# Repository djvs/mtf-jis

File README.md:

# MtF-JIS Capacitive Conversion PCB for IBM Model M JIS Keyboards

Forked from ViviLazuli/mtf-capacitive

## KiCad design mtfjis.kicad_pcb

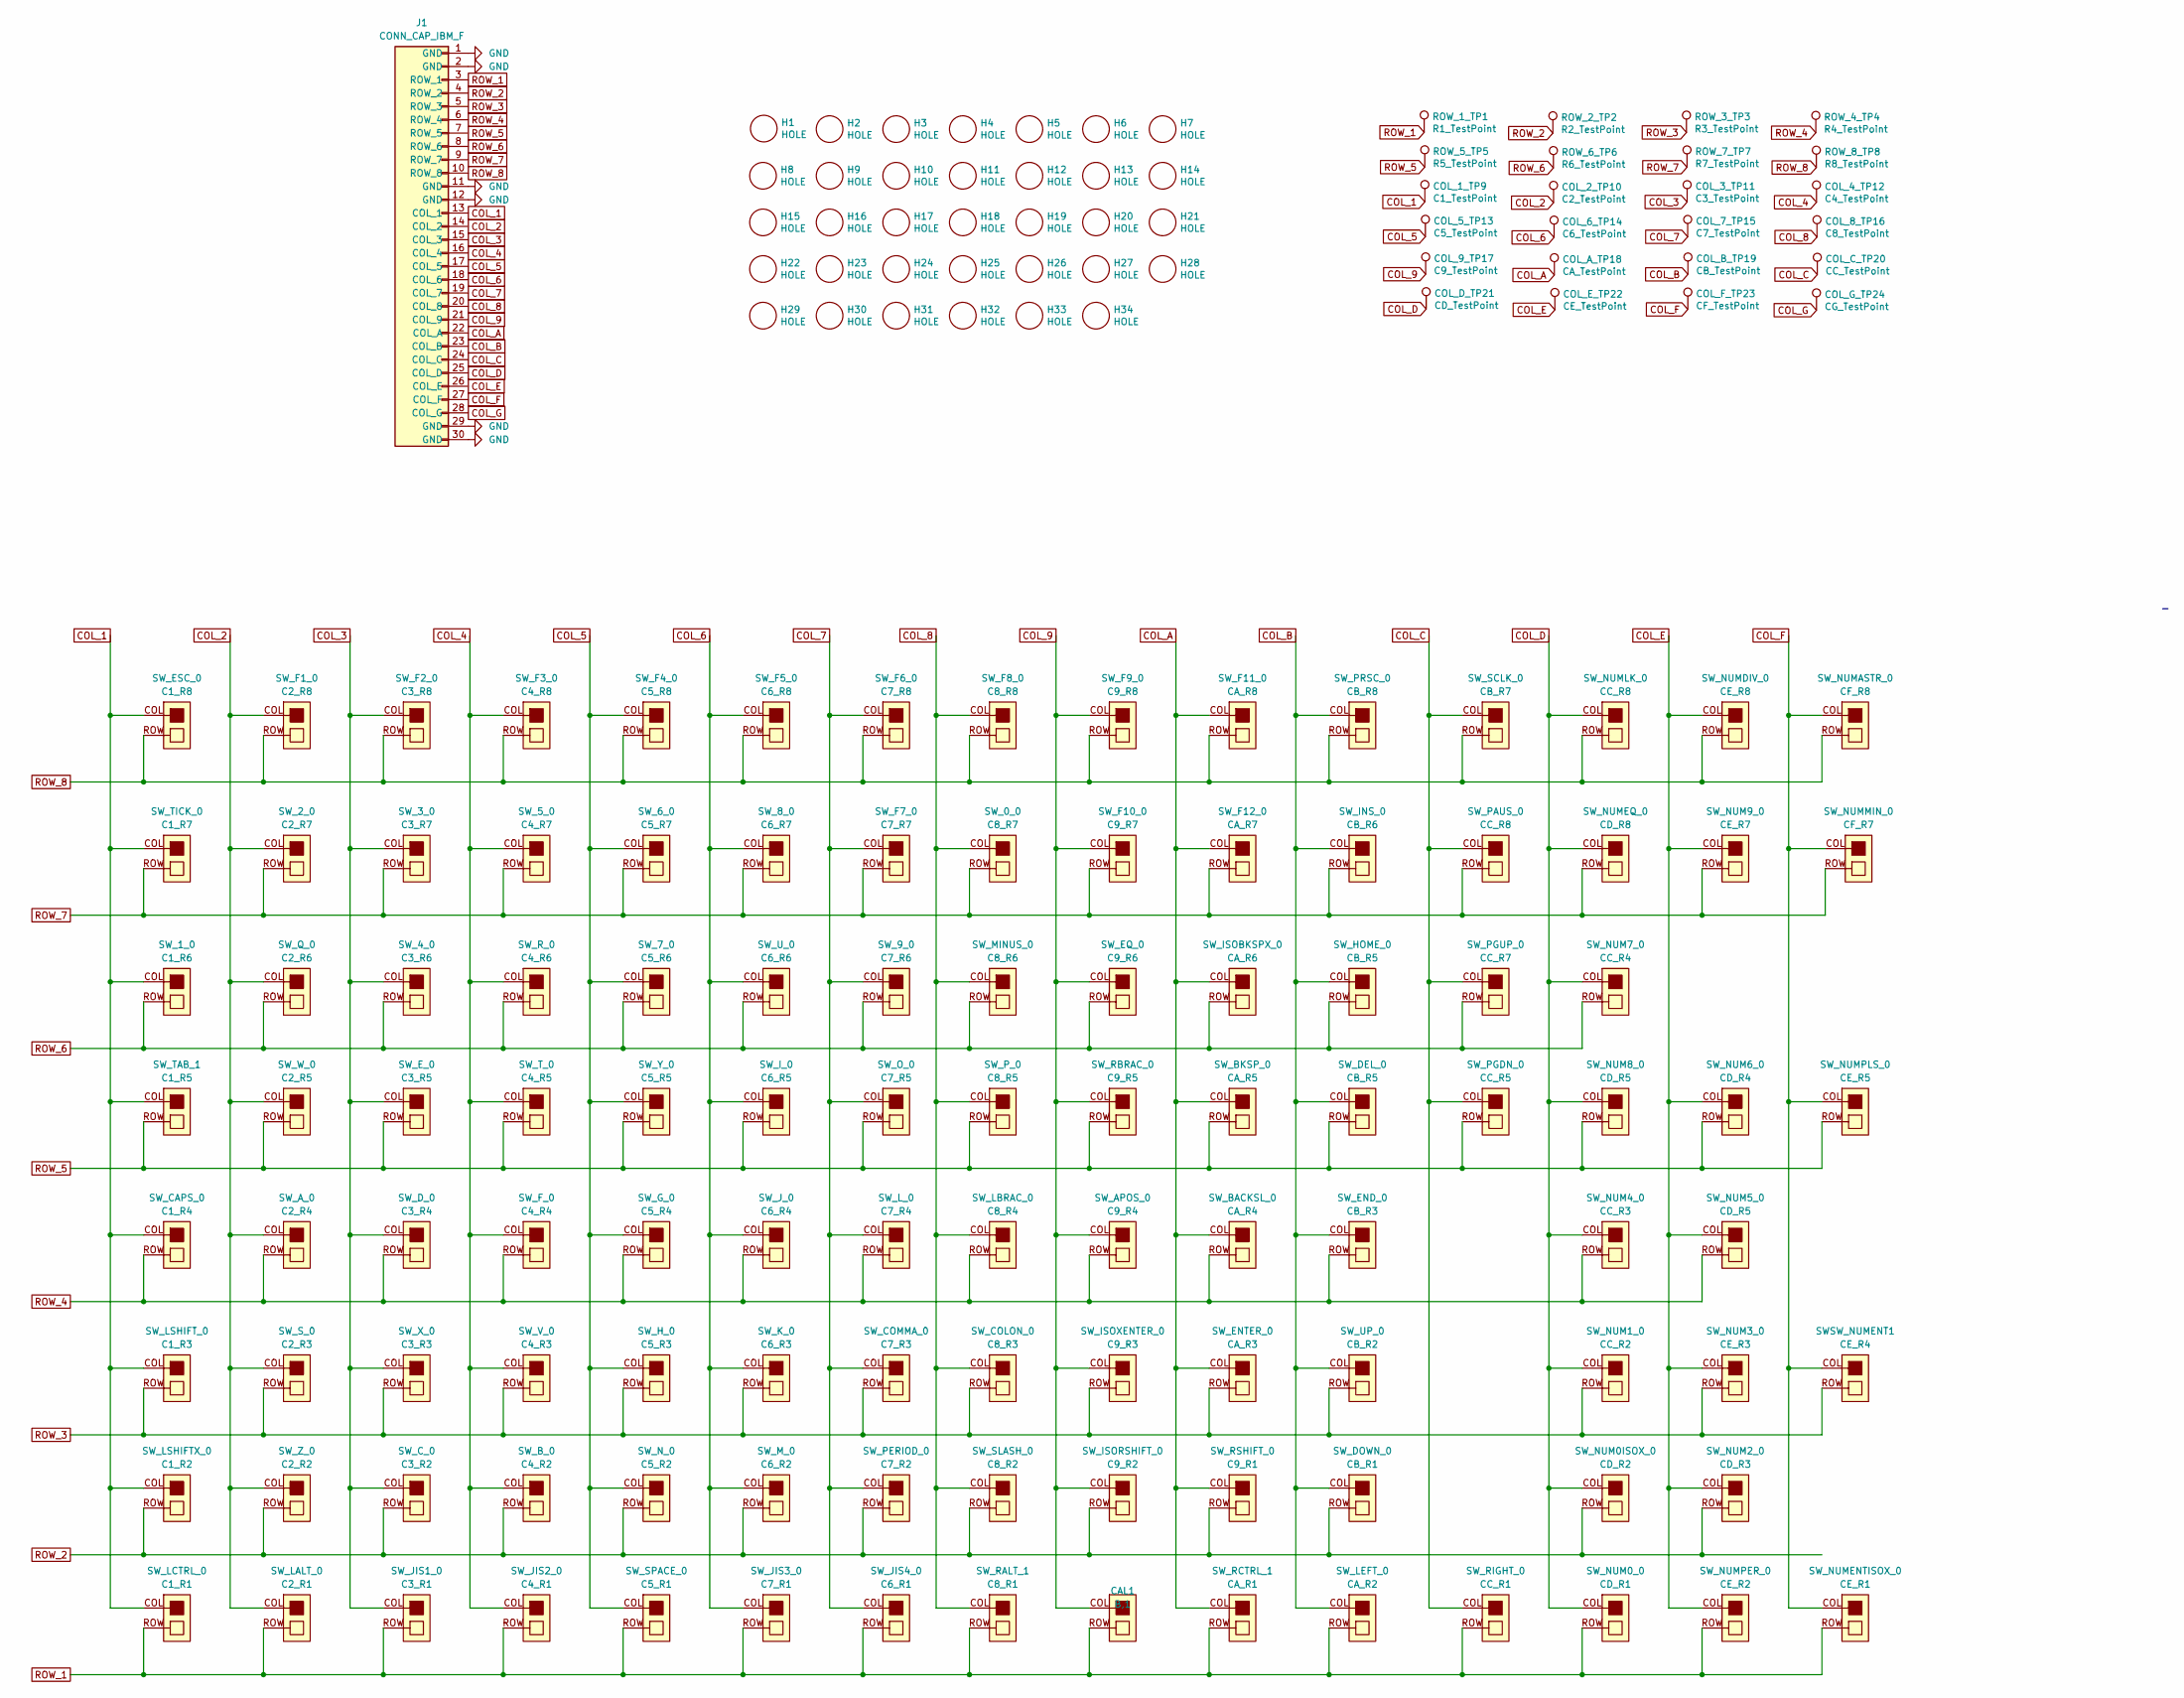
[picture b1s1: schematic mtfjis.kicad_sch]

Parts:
CAL1: B,1; CAL_CAP_IBM_F
COL_1_TP9: C1_TestPoint; TestPoint_Pad_D1.0mm
COL_2_TP10: C2_TestPoint; TestPoint_Pad_D1.0mm
COL_3_TP11: C3_TestPoint; TestPoint_Pad_D1.0mm
COL_4_TP12: C4_TestPoint; TestPoint_Pad_D1.0mm
COL_5_TP13: C5_TestPoint; TestPoint_Pad_D1.0mm
COL_6_TP14: C6_TestPoint; TestPoint_Pad_D1.0mm
COL_7_TP15: C7_TestPoint; TestPoint_Pad_D1.0mm
COL_8_TP16: C8_TestPoint; TestPoint_Pad_D1.0mm
COL_9_TP17: C9_TestPoint; TestPoint_Pad_D1.0mm
COL_A_TP18: CA_TestPoint; TestPoint_Pad_D1.0mm
COL_B_TP19: CB_TestPoint; TestPoint_Pad_D1.0mm
COL_C_TP20: CC_TestPoint; TestPoint_Pad_D1.0mm
COL_D_TP21: CD_TestPoint; TestPoint_Pad_D1.0mm
COL_E_TP22: CE_TestPoint; TestPoint_Pad_D1.0mm
COL_F_TP23: CF_TestPoint; TestPoint_Pad_D1.0mm
COL_G_TP24: CG_TestPoint; TestPoint_Pad_D1.0mm
H1, H2, H3, H4, H5, H6, H7, H8, H9, H10, H11, H12, H13, H14, H15, H16, H17, H18, H19, H20, H21, H22, H23, H24, H25, H26, H27, H28, H29, H30, H31, H32, H33, H34: HOLE
J1: CONN_CAP_IBM_F
ROW_1_TP1: R1_TestPoint; TestPoint_Pad_D1.0mm
ROW_2_TP2: R2_TestPoint; TestPoint_Pad_D1.0mm
ROW_3_TP3: R3_TestPoint; TestPoint_Pad_D1.0mm
ROW_4_TP4: R4_TestPoint; TestPoint_Pad_D1.0mm
ROW_5_TP5: R5_TestPoint; TestPoint_Pad_D1.0mm
ROW_6_TP6: R6_TestPoint; TestPoint_Pad_D1.0mm
ROW_7_TP7: R7_TestPoint; TestPoint_Pad_D1.0mm
ROW_8_TP8: R8_TestPoint; TestPoint_Pad_D1.0mm
SWSW_NUMENT1: CE_R4; SW_CAP_IBM_F
SW_0_0: C8_R7; SW_CAP_IBM_F
SW_1_0: C1_R6; SW_CAP_IBM_F_ALT
SW_2_0: C2_R7; SW_CAP_IBM_F
SW_3_0: C3_R7; SW_CAP_IBM_F
SW_4_0: C3_R6; SW_CAP_IBM_F_ALT
SW_5_0: C4_R7; SW_CAP_IBM_F
SW_6_0: C5_R7; SW_CAP_IBM_F
SW_7_0: C5_R6; SW_CAP_IBM_F_ALT
SW_8_0: C6_R7; SW_CAP_IBM_F_ALT
SW_9_0: C7_R6; SW_CAP_IBM_F_ALT
SW_APOS_0: C9_R4; SW_CAP_IBM_F
SW_A_0: C2_R4; SW_CAP_IBM_F
SW_BACKSL_0: CA_R4; SW_CAP_IBM_F
SW_BKSP_0: CA_R5; SW_CAP_IBM_F_ALT
SW_B_0: C4_R2; SW_CAP_IBM_F_ALT
SW_CAPS_0: C1_R4; SW_CAP_IBM_F
SW_COLON_0: C8_R3; SW_CAP_IBM_F
SW_COMMA_0: C7_R3; SW_CAP_IBM_F
SW_C_0: C3_R2; SW_CAP_IBM_F_ALT
SW_DEL_0: CB_R5; SW_CAP_IBM_F
SW_DOWN_0: CB_R1; SW_CAP_IBM_F_ALT
SW_D_0: C3_R4; SW_CAP_IBM_F
SW_END_0: CB_R3; SW_CAP_IBM_F_ALT
SW_ENTER_0: CA_R3; SW_CAP_IBM_F
SW_EQ_0: C9_R6; SW_CAP_IBM_F_ALT
SW_ESC_0: C1_R8; SW_CAP_IBM_F
SW_E_0: C3_R5; SW_CAP_IBM_F
SW_F1_0: C2_R8; SW_CAP_IBM_F
SW_F2_0: C3_R8; SW_CAP_IBM_F
SW_F3_0: C4_R8; SW_CAP_IBM_F_ALT
SW_F4_0: C5_R8; SW_CAP_IBM_F
SW_F5_0: C6_R8; SW_CAP_IBM_F
SW_F6_0: C7_R8; SW_CAP_IBM_F
SW_F7_0: C7_R7; SW_CAP_IBM_F_ALT
SW_F8_0: C8_R8; SW_CAP_IBM_F
SW_F9_0: C9_R8; SW_CAP_IBM_F
SW_F10_0: C9_R7; SW_CAP_IBM_F_ALT
SW_F11_0: CA_R8; SW_CAP_IBM_F
SW_F12_0: CA_R7; SW_CAP_IBM_F_ALT
SW_F_0: C4_R4; SW_CAP_IBM_F
SW_G_0: C5_R4; SW_CAP_IBM_F
SW_HOME_0: CB_R5; SW_CAP_IBM_F_ALT
SW_H_0: C5_R3; SW_CAP_IBM_F_ALT
SW_INS_0: CB_R6; SW_CAP_IBM_F
SW_ISOBKSPX_0: CA_R6; SW_CAP_IBM_F
SW_ISORSHIFT_0: C9_R2; SW_CAP_IBM_F
SW_ISOXENTER_0: C9_R3; SW_CAP_IBM_F_ALT
SW_I_0: C6_R5; SW_CAP_IBM_F_ALT
SW_JIS1_0: C3_R1; SW_CAP_IBM_F_ALT
SW_JIS2_0: C4_R1; SW_CAP_IBM_F_ALT
SW_JIS3_0: C7_R1; SW_CAP_IBM_F_ALT
SW_JIS4_0: C6_R1; SW_CAP_IBM_F_ALT
SW_J_0: C6_R4; SW_CAP_IBM_F
SW_K_0: C6_R3; SW_CAP_IBM_F_ALT
SW_LALT_0: C2_R1; SW_CAP_IBM_F_ALT
SW_LBRAC_0: C8_R4; SW_CAP_IBM_F_ALT
SW_LCTRL_0: C1_R1; SW_CAP_IBM_F
SW_LEFT_0: CA_R2; SW_CAP_IBM_F
SW_LSHIFTX_0: C1_R2; SW_CAP_IBM_F_ALT
SW_LSHIFT_0: C1_R3; SW_CAP_IBM_F
SW_L_0: C7_R4; SW_CAP_IBM_F_ALT
SW_MINUS_0: C8_R6; SW_CAP_IBM_F_ALT
SW_M_0: C6_R2; SW_CAP_IBM_F_ALT
SW_NUM0ISOX_0: CD_R2; SW_CAP_IBM_F_ALT
SW_NUM0_0: CD_R1; SW_CAP_IBM_F
SW_NUM1_0: CC_R2; SW_CAP_IBM_F
SW_NUM2_0: CD_R3; SW_CAP_IBM_F
SW_NUM3_0: CE_R3; SW_CAP_IBM_F_ALT
SW_NUM4_0: CC_R3; SW_CAP_IBM_F
SW_NUM5_0: CD_R5; SW_CAP_IBM_F
SW_NUM6_0: CD_R4; SW_CAP_IBM_F_ALT
SW_NUM7_0: CC_R4; SW_CAP_IBM_F
SW_NUM8_0: CD_R5; SW_CAP_IBM_F_ALT
SW_NUM9_0: CE_R7; SW_CAP_IBM_F
SW_NUMASTR_0: CF_R8; SW_CAP_IBM_F
SW_NUMDIV_0: CE_R8; SW_CAP_IBM_F
SW_NUMENTISOX_0: CE_R1; SW_CAP_IBM_F
SW_NUMEQ_0: CD_R8; SW_CAP_IBM_F_ALT
SW_NUMLK_0: CC_R8; SW_CAP_IBM_F
SW_NUMMIN_0: CF_R7; SW_CAP_IBM_F
SW_NUMPER_0: CE_R2; SW_CAP_IBM_F_ALT
SW_NUMPLS_0: CE_R5; SW_CAP_IBM_F
SW_N_0: C5_R2; SW_CAP_IBM_F_ALT
SW_O_0: C7_R5; SW_CAP_IBM_F_ALT
SW_PAUS_0: CC_R8; SW_CAP_IBM_F_ALT
SW_PERIOD_0: C7_R2; SW_CAP_IBM_F_ALT
SW_PGDN_0: CC_R5; SW_CAP_IBM_F
SW_PGUP_0: CC_R7; SW_CAP_IBM_F
SW_PRSC_0: CB_R8; SW_CAP_IBM_F
SW_P_0: C8_R5; SW_CAP_IBM_F
SW_Q_0: C2_R6; SW_CAP_IBM_F_ALT
SW_RALT_1: C8_R1; SW_CAP_IBM_F_ALT
SW_RBRAC_0: C9_R5; SW_CAP_IBM_F_ALT
SW_RCTRL_1: CA_R1; SW_CAP_IBM_F
SW_RIGHT_0: CC_R1; SW_CAP_IBM_F
SW_RSHIFT_0: C9_R1; SW_CAP_IBM_F
SW_R_0: C4_R6; SW_CAP_IBM_F
SW_SCLK_0: CB_R7; SW_CAP_IBM_F
SW_SLASH_0: C8_R2; SW_CAP_IBM_F_ALT
SW_SPACE_0: C5_R1; SW_CAP_IBM_F_ALT
SW_S_0: C2_R3; SW_CAP_IBM_F_ALT
SW_TAB_1: C1_R5; SW_CAP_IBM_F
SW_TICK_0: C1_R7; SW_CAP_IBM_F
SW_T_0: C4_R5; SW_CAP_IBM_F_ALT
SW_UP_0: CB_R2; SW_CAP_IBM_F_ALT
SW_U_0: C6_R6; SW_CAP_IBM_F
SW_V_0: C4_R3; SW_CAP_IBM_F
SW_W_0: C2_R5; SW_CAP_IBM_F
SW_X_0: C3_R3; SW_CAP_IBM_F
SW_Y_0: C5_R5; SW_CAP_IBM_F_ALT
SW_Z_0: C2_R2; SW_CAP_IBM_F

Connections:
COL_1: COL_1_TP9.1, J1.13 (COL_1), SW_1_0.COL, SW_CAPS_0.COL, SW_ESC_0.COL, SW_LCTRL_0.COL, SW_LSHIFTX_0.COL, SW_LSHIFT_0.COL, SW_TAB_1.COL, SW_TICK_0.COL
COL_2: COL_2_TP10.1, J1.14 (COL_2), SW_2_0.COL, SW_A_0.COL, SW_F1_0.COL, SW_LALT_0.COL, SW_Q_0.COL, SW_S_0.COL, SW_W_0.COL, SW_Z_0.COL
COL_3: COL_3_TP11.1, J1.15 (COL_3), SW_3_0.COL, SW_4_0.COL, SW_C_0.COL, SW_D_0.COL, SW_E_0.COL, SW_F2_0.COL, SW_JIS1_0.COL, SW_X_0.COL
COL_4: COL_4_TP12.1, J1.16 (COL_4), SW_5_0.COL, SW_B_0.COL, SW_F3_0.COL, SW_F_0.COL, SW_JIS2_0.COL, SW_R_0.COL, SW_T_0.COL, SW_V_0.COL
COL_5: COL_5_TP13.1, J1.17 (COL_5), SW_6_0.COL, SW_7_0.COL, SW_F4_0.COL, SW_G_0.COL, SW_H_0.COL, SW_N_0.COL, SW_SPACE_0.COL, SW_Y_0.COL
COL_6: COL_6_TP14.1, J1.18 (COL_6), SW_8_0.COL, SW_F5_0.COL, SW_I_0.COL, SW_JIS3_0.COL, SW_J_0.COL, SW_K_0.COL, SW_M_0.COL, SW_U_0.COL
COL_7: COL_7_TP15.1, J1.19 (COL_7), SW_9_0.COL, SW_COMMA_0.COL, SW_F6_0.COL, SW_F7_0.COL, SW_JIS4_0.COL, SW_L_0.COL, SW_O_0.COL, SW_PERIOD_0.COL
COL_8: COL_8_TP16.1, J1.20 (COL_8), SW_0_0.COL, SW_COLON_0.COL, SW_F8_0.COL, SW_LBRAC_0.COL, SW_MINUS_0.COL, SW_P_0.COL, SW_RALT_1.COL, SW_SLASH_0.COL
COL_9: CAL1.COL, COL_9_TP17.1, J1.21 (COL_9), SW_APOS_0.COL, SW_EQ_0.COL, SW_F9_0.COL, SW_F10_0.COL, SW_ISORSHIFT_0.COL, SW_ISOXENTER_0.COL, SW_RBRAC_0.COL
COL_A: COL_A_TP18.1, J1.22 (COL_A), SW_BACKSL_0.COL, SW_BKSP_0.COL, SW_ENTER_0.COL, SW_F11_0.COL, SW_F12_0.COL, SW_ISOBKSPX_0.COL, SW_RCTRL_1.COL, SW_RSHIFT_0.COL
COL_B: COL_B_TP19.1, J1.23 (COL_B), SW_DEL_0.COL, SW_DOWN_0.COL, SW_END_0.COL, SW_HOME_0.COL, SW_INS_0.COL, SW_LEFT_0.COL, SW_PRSC_0.COL, SW_UP_0.COL
COL_C: COL_C_TP20.1, J1.24 (COL_C), SW_PAUS_0.COL, SW_PGDN_0.COL, SW_PGUP_0.COL, SW_RIGHT_0.COL, SW_SCLK_0.COL
COL_D: COL_D_TP21.1, J1.25 (COL_D), SW_NUM0ISOX_0.COL, SW_NUM0_0.COL, SW_NUM1_0.COL, SW_NUM4_0.COL, SW_NUM7_0.COL, SW_NUM8_0.COL, SW_NUMEQ_0.COL, SW_NUMLK_0.COL
COL_E: COL_E_TP22.1, J1.26 (COL_E), SW_NUM2_0.COL, SW_NUM3_0.COL, SW_NUM5_0.COL, SW_NUM6_0.COL, SW_NUM9_0.COL, SW_NUMDIV_0.COL, SW_NUMPER_0.COL
COL_F: COL_F_TP23.1, J1.27 (COL_F), SWSW_NUMENT1.COL, SW_NUMASTR_0.COL, SW_NUMENTISOX_0.COL, SW_NUMMIN_0.COL, SW_NUMPLS_0.COL
COL_G: COL_G_TP24.1, J1.28 (COL_G)
GND: J1.1 (GND), J1.2 (GND), J1.11 (GND), J1.12 (GND), J1.29 (GND), J1.30 (GND)
ROW_1: CAL1.ROW, J1.3 (ROW_1), ROW_1_TP1.1, SW_JIS1_0.ROW, SW_JIS2_0.ROW, SW_JIS3_0.ROW, SW_JIS4_0.ROW, SW_LALT_0.ROW, SW_LCTRL_0.ROW, SW_LEFT_0.ROW, SW_NUM0_0.ROW, SW_NUMENTISOX_0.ROW, SW_NUMPER_0.ROW, SW_RALT_1.ROW, SW_RCTRL_1.ROW, SW_RIGHT_0.ROW, SW_SPACE_0.ROW
ROW_2: J1.4 (ROW_2), ROW_2_TP2.1, SW_B_0.ROW, SW_C_0.ROW, SW_DOWN_0.ROW, SW_ISORSHIFT_0.ROW, SW_LSHIFTX_0.ROW, SW_M_0.ROW, SW_NUM0ISOX_0.ROW, SW_NUM2_0.ROW, SW_N_0.ROW, SW_PERIOD_0.ROW, SW_RSHIFT_0.ROW, SW_SLASH_0.ROW, SW_Z_0.ROW
ROW_3: J1.5 (ROW_3), ROW_3_TP3.1, SWSW_NUMENT1.ROW, SW_COLON_0.ROW, SW_COMMA_0.ROW, SW_ENTER_0.ROW, SW_H_0.ROW, SW_ISOXENTER_0.ROW, SW_K_0.ROW, SW_LSHIFT_0.ROW, SW_NUM1_0.ROW, SW_NUM3_0.ROW, SW_S_0.ROW, SW_UP_0.ROW, SW_V_0.ROW, SW_X_0.ROW
ROW_4: J1.6 (ROW_4), ROW_4_TP4.1, SW_APOS_0.ROW, SW_A_0.ROW, SW_BACKSL_0.ROW, SW_CAPS_0.ROW, SW_D_0.ROW, SW_END_0.ROW, SW_F_0.ROW, SW_G_0.ROW, SW_J_0.ROW, SW_LBRAC_0.ROW, SW_L_0.ROW, SW_NUM4_0.ROW, SW_NUM5_0.ROW
ROW_5: J1.7 (ROW_5), ROW_5_TP5.1, SW_BKSP_0.ROW, SW_DEL_0.ROW, SW_E_0.ROW, SW_I_0.ROW, SW_NUM6_0.ROW, SW_NUM8_0.ROW, SW_NUMPLS_0.ROW, SW_O_0.ROW, SW_PGDN_0.ROW, SW_P_0.ROW, SW_RBRAC_0.ROW, SW_TAB_1.ROW, SW_T_0.ROW, SW_W_0.ROW, SW_Y_0.ROW
ROW_6: J1.8 (ROW_6), ROW_6_TP6.1, SW_1_0.ROW, SW_4_0.ROW, SW_7_0.ROW, SW_9_0.ROW, SW_EQ_0.ROW, SW_HOME_0.ROW, SW_ISOBKSPX_0.ROW, SW_MINUS_0.ROW, SW_NUM7_0.ROW, SW_PGUP_0.ROW, SW_Q_0.ROW, SW_R_0.ROW, SW_U_0.ROW
ROW_7: J1.9 (ROW_7), ROW_7_TP7.1, SW_0_0.ROW, SW_2_0.ROW, SW_3_0.ROW, SW_5_0.ROW, SW_6_0.ROW, SW_8_0.ROW, SW_F7_0.ROW, SW_F10_0.ROW, SW_F12_0.ROW, SW_INS_0.ROW, SW_NUM9_0.ROW, SW_NUMEQ_0.ROW, SW_NUMMIN_0.ROW, SW_PAUS_0.ROW, SW_TICK_0.ROW
ROW_8: J1.10 (ROW_8), ROW_8_TP8.1, SW_ESC_0.ROW, SW_F1_0.ROW, SW_F2_0.ROW, SW_F3_0.ROW, SW_F4_0.ROW, SW_F5_0.ROW, SW_F6_0.ROW, SW_F8_0.ROW, SW_F9_0.ROW, SW_F11_0.ROW, SW_NUMASTR_0.ROW, SW_NUMDIV_0.ROW, SW_NUMLK_0.ROW, SW_PRSC_0.ROW, SW_SCLK_0.ROW

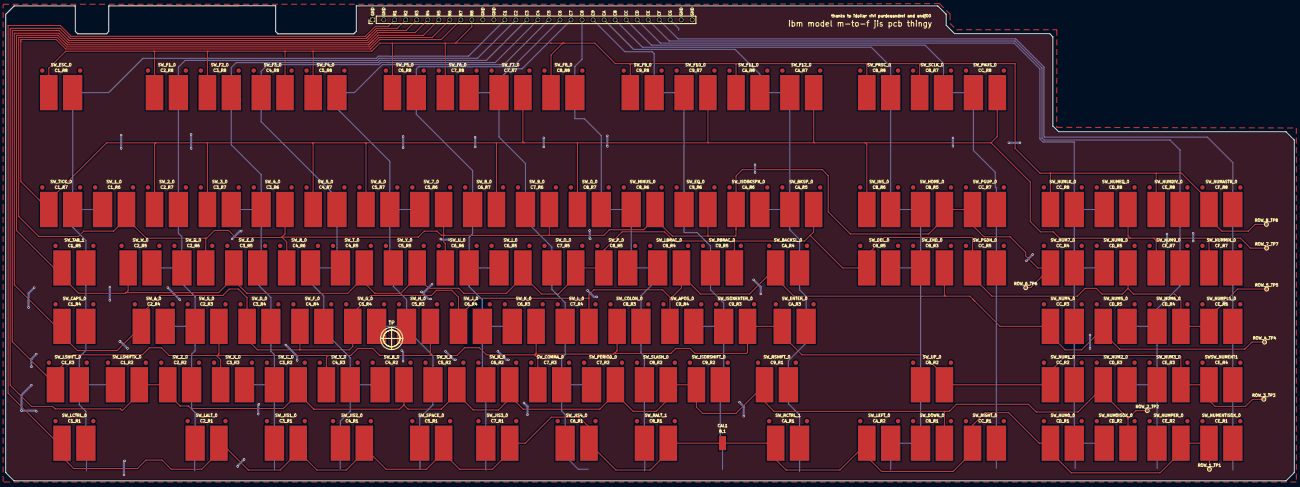
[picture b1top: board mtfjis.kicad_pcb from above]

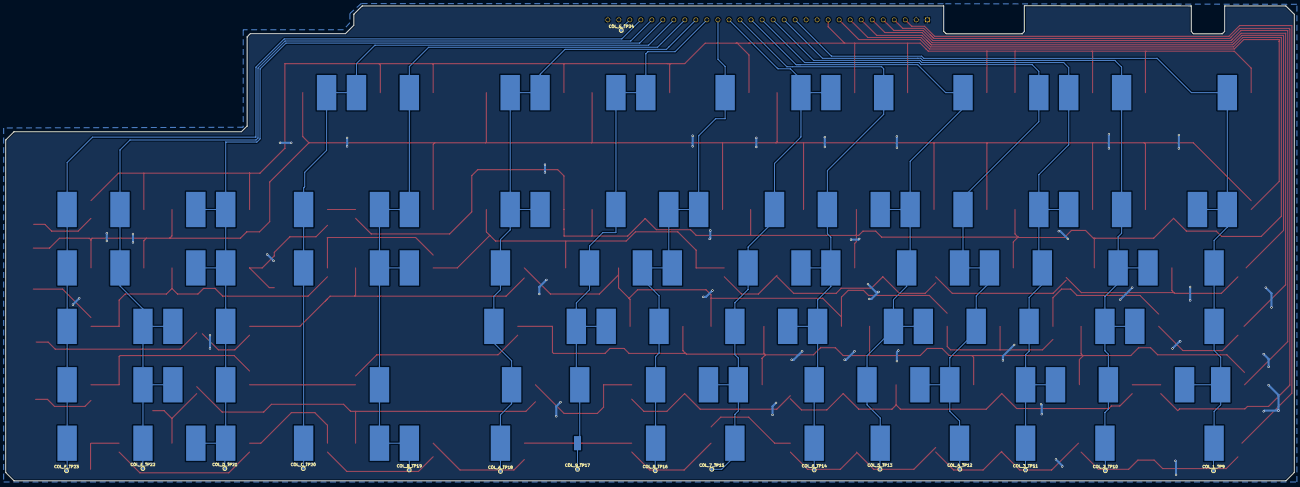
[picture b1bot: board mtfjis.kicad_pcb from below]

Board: 2 copper layers, 463.2 x 170.8 mm, 201 parts (16 on the bottom side), 25 nets.

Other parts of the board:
H35, H36, H37, H38, H39, H40, H41, H42, H43, H44, H45, H46, H47, H48, H49, H50, H51, H52, H53, H54, H55, H56, H57, H58, H59, H60, H61, H62, H63: HOLE

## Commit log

2021-08-25 starting over
2021-08-25 gitignore mtfjis-backups, wipe tracks and update schematic
2021-08-26 main details roughed out
2021-08-30 save progress
2021-09-06 host flipper cad
